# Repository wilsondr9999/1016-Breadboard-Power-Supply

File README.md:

# BreadBrick
#### The breadboard power supply *with flair*

## Why Another Breadboard Power Supply?

There's a million of these things out there, and they all work pretty much the same.  They plug in on one end of the breadboard and supply power to the voltage rails.  Many do 5V only, some have switchable 5V / 3.3V using jumpers.  Many use linear power regulators which are not terribly efficient.  Many have substantial voltage droop.  Many can't supply very much current.

I wanted something with a bit more, ummm, pizazz.  I wanted a case, not a bare PCB.  I wanted the ability to set the voltage independently for each rail, indicator lights for what voltages are set, up to 2A / 10W on each rail, and protection circuitry for those times when you plug something into the breadboard backwards.  And some efficiency so the thing doesn't get hot.

It took me a while, but I did it.

## Design

The design of the unit is actually not too complicated, there is an input section for protection and filtering, three [Texas Instruments TPS62130A](https://www.ti.com/product/TPS62130A) switching buck regulator circuits, two for the two power rails, and a 3rd that generates a dedicated 3.3V for the MCU, and an MCU section that uses the [STM32C011F4](https://www.st.com/en/microcontrollers-microprocessors/stm32c011f4.html).  The MCU is used to get user input from the buttons, drive the indicator LEDs, and control and monitor the rail regulators.

All components were selected for reasonable cost and wide availability.  However, the design is at the limit of what a hobbyist can successfully assemble.  While no parts smaller than 0603 are used, some ICs are QFN, and hand soldering these parts can be difficult for the hobbyists.  This board can be assembled by board assembly services at a reasonable cost.

## Tools and Software

Circuit design, schematics, and PCB layout were all done with [KiCad](https://www.kicad.org/).  Design of the case was done in [FreeCAD](https://www.freecad.org/).  Software code for the STM32C0 was written, compiled, and debugged using the [STM32CubeIDE](https://www.st.com/en/development-tools/stm32cubeide.html) development environment.

## Licensing

Several different licenses apply to this repository and the files within.

All schematics and circuit board designs in the project (all KiCad files), as well as all case designs (all FreeCAD files) are licensed under the [CERN Open Hardware License Version 2 - Strongly Reciprocal (CERN-OHL-S)](LICENSE-CERN-OHL-S).

All software and firmware code in the project (all ) are licensed under the [GNU Affero General Public License v3.0 (AGPL 3.0)](LICENSE-AGPL).

Documentation, Bill of Materials, pictures, and documentation (i.e. all other files not covered by the other two licenses above) are licensed under the [Creative Commons Attribution Share Alike 4.0 International License (CC-BY-SA-4.0)](LICENSE-CC-BY-SA-4.0).

These licenses form a very restrictive license for this design and this project.  This is done specifically for a reason.  That reason is that this project is for the hobbyist, and the hobbyist only.  It is for those people who want to have one of these units to be able to make one for themselves.  What it is not for is for some no-name company to produce thousands of them and make money when they had nothing to do with the design and the hard work.  These licenses force anyone who wants to do that to share anything and everything that they derive from this work so that the community and the hobbyists have it also.

## Specifications
- Input Voltage: 7V - 17V
- DC Barrel Jack: 2.5mm ID x 5.5mm OD, Center pin is positive (+)
- Max Input Current: 2A
- Output Voltage: 5V +/- 0.05V, 3.3V +/- 0.05V, switchable per rail
- Output Voltage Ripple: 25 mV at 2A load
- Max Output Current: 2A per rail
- Typical Efficiency: 88.0% at 12V input and 5V / 1A output
- Worst-Case Efficiency: 84.0% at 17V input and 3.3V / 2A output
- Worst-Case heat sink temperature: 51.1 C at full 2A load

## How To Build
#### Ordering the PCB
To order this PCB, you can submit the [Fabrication Exports.zip](KiCAD%20Project/Fabrication%20Exports/Fabrication%20Exports.zip) file (located in [KiCAD Project/Fabrication Exports/](KiCAD%20Project/Fabrication%20Exports/)) to your favorite PCB manufacturing company.  This is a 2 layer board so costs should be low.
#### Ordering the Stencil
If you want to assemble the board yourself, especially if you want to use a reflow oven, you can order a stencil using the [1016 Breadboard Power Supply-F_Paste.gbr](KiCAD%20Project/Fabrication%20Exports/1016%20Breadboard%20Power%20Supply-F_Paste.gbr) gerber layer.  This layer includes 2.5mm alignment pins on two corners, these are sized and located to fit on the [solder stencil jig](FreeCAD%20Project/Parametric%20Solder%20Stencil%20Jig/1016%20v2%20Parametric%20Solder%20Stencil%20Jig.3mf) that can be 3D-printed.  If instead you are having a PCB manufacturer assemble the SMD components for you, you do not need the solder stencil.
#### Ordering Parts
If you're assembling yourself, you'll need to order parts.  The [1016 Breadboard Power Supply.csv](KiCAD%20Project/BOM/1016%20Breadboard%20Power%20Supply.csv) file located in the [KiCAD Project/BOM/](KiCAD%20Project/BOM/) folder contains all parts and manufacturer part numbers.
#### Assembling the PCB
The [ibom.html](KiCAD%20Project/BOM/ibom.html) file located in the [KiCAD Project/BOM/](KiCAD%20Project/BOM/) folder is generated from the [KiCad Interactive BOM plug-in](https://github.com/openscopeproject/InteractiveHtmlBom), and can help you mark which parts have been placed on the board prior to reflow.

Be very careful placing the LEDs.  The silkscreen marks pin 1 of the LED, but in accordance with the [datasheets](Datasheets/[DS-006]%20Wurth%20Elektronik%20150060VS75003.pdf) for the Wurth Elektronik LEDs, the pin 1 marking is NOT the cathode as would normally be expected.

After placing components, reflow the board in a reflow oven, hot plate, or use a hot air station.
#### Through-Hole Components
You will need to solder three through-hole components -- the DC power jack (PJ-102B), and the 2x2 pin headers (J3/J4).
#### Heat Sinks
The two heat sinks are glued onto the back side of the board using thermal adhesive.  Note that this is thermal adhesive (glue), not just an ordinary thermal compound or thermal paste.  The adhesive is required, there is no other mechanical support for the heat sinks.  I successfully used the [Gennel G109 Thermal Conductive Glue](https://www.amazon.com/dp/B072MSXHJD?psc=1&ref=ppx_yo2ov_dt_b_product_details).
#### 3D Printing the Case
The case can be 3D printed using the [Case Top-Bottom.3mf](FreeCAD%20Project/Case/STL/Case%20Top-Bottom.3mf), [Button.3mf](FreeCAD%20Project/Case/STL/Button.3mf), and [LED Lens.3mf](FreeCAD%20Project/Case/STL/LED%20Lens.3mf) files and [PrusaSlicer](https://www.prusa3d.com/page/prusaslicer_424/), or if you want to slice the .stl files yourself, the .stl files are also included in the [FreeCAD Project/Case/STL](FreeCAD%20Project/Case/STL/) folder.  Printing settings are as follows:
- 0.12mm Layer Height
- 0.4mm Nozzle
- PETG material, do not use PLA.  The snap-together design needs a flexible plastic, PLA is too brittle and will likely break when trying to snap together the case.  Also, PLA is not as temperature-resistant as PETG, and the heat sinks could cause problems with PLA.
- For the LED lenses, you will need a clear PETG filament.  I have had good results with [PolyMaker PolyLite Clear PETG](https://us.polymaker.com/products/polylite-petg?variant=41266031099961).
- Supports are not required, but both case halves should be printed with their flat surface on the print bed.  You may need to turn the upper case half so that the flat top is on the print bed.  The LED lenses need to be turned so that the larger side is down on the print bed.
- The upper case half prints with a thin bridge covering the LED lens holes, you will need to clean out the bridges with a hobbyist knife prior to inserting the LED lenses.
- It is critical that the buttons are printed to accurate dimensions as the clearances and travel are very small.  Print the buttons at a very slow speed with adequate time for each layer to cool to prevent any warping or distortion.  The .3mf file already has these settings pre-set.
#### Programming Firmware to the STM32
The STM32C011F4 firmware is the [1016 Breadboard Power Supply.elf](STM32%20Project/Debug/1016%20Breaadboard%20Power%20Supply.elf) file located in the [(STM32 Project/Debug/]((STM32%20Project/Debug/) folder.  This can be programmed to the STM32C011F4 using the [ST-Link/V2](https://www.st.com/en/development-tools/st-link-v2.html) debugger and the [Tag-Connect ARM20-CTX SWD Solution](https://www.tag-connect.com/debugger-cable-selection-installation-instructions/st-link-v2#49_126_145).  The 6-pin Tag-Connect connector connects with the J2 connector on the PCB, and the [STM32CubeProgrammer](https://www.st.com/en/development-tools/stm32cubeprog.html) software can write the firmware to the MCU.

Note that if you order the Tag-Connect SWD solution, you need the "No-Legs" version of the package that includes the TC-2030-IDC-NL cable.  The version of the cable with legs (TC-2030-IDC) will not properly fit this PCB.
#### Assembling the Unit
Once the PCB has been populated and soldered with the SMD and THT components, the heat sinks are attached with the thermal adhesive, and the case parts have been printed you can assemble the entire unit.
- Turn the upper half of the case upside down, and insert the two buttons, aligning the base of the buttons so that they will fit over the SMD switches on the PCB.
- Place the PCB into the top side of the case with the components towards the buttons and the heat sinks protruding.  Ensure the base of the buttons goes over the SMD switches on the PCB.  Hold the PCB against the support columns with your fingers.
- Test the buttons on the other side of the case and ensure you can feel them actuate the switches and that the switches are NOT pressed when the PCB is seated against the support columns.
- If the switches are not getting pressed when you press the button, the buttons dimensions are too small.  Re-check your print settings.
- If the switches are getting pressed before the PCB is seated against the support columns, the buttons dimensions are too large.  Re-check your print settings.
- Once you are confident that the buttons are the correct size and will work, remove the PCB from the top case half.
- Tape the buttons in place on the top side.  Fold the tape around the protruding button so that the button is at the top of it's travel (most protrusion).
- Insert the PCB into the case bottom with the components up and the heat sinks down.  The heat sinks will fit inside the cooling passages, and the holes in the PCB will fit on the support pins.
- Carefully fit the top half with the taped buttons onto the bottom half, and carefully get the two halves to mate and snap together.
- Remove the tape from the buttons and re-check that the buttons are working properly.  If you need to get the case apart again, you will need to use a [spudger](https://www.amazon.com/MMOBIEL-Pieces-Professional-Spudger-Toolkit/dp/B00UNBTM5U/ref=sr_1_4?keywords=spudger&sr=8-4) to pry the case apart.

## Using the Breadboard Power Supply
Plug the unit into your breadboard into the power rails.  As you're looking at the unit, the power arms/leads should point towards your right.  In this position, the TOP pins of each rail (furthest away from you) are the positive voltage, the BOTTOM pins of each rail (closest to you) are the reference voltage (ground).  Orient your breadboard so that the red/positive row of pins aligns with the positive pin of the unit (away from you).  If your breadboard is turned 180 degrees, the colors of the power rails will be opposite, and will cause confusion.

Power the unit using a DC barrel jack and power supply.  The jack is a standard 2.5mm x 5.5mm DC barrel jack, the center pin is the positive lead.  The unit has reverse power protection, so if your power supply uses ground for the center pin, you will not damage the unit, but it will not power on.  Your power supply should be between 7V and 17V output, and should provide at least 24W of power.  The standard supply that the unit was designed for is a [12V, 2A supply](https://www.amazon.com/Chanzon-Switching-Adapter-100-240V-Transformer/dp/B07HNL5D56/ref=sr_1_19?keywords=12v+2a+power+supply&sr=8-19).  

Once the unit is powered on, it will self-test all LEDs.  You should see them sequentially light.

The left-most LED is the power-on LED, and indicates that input power is being received and is the correct voltage and polarity.  The LED remains green at all times when input power is supplied.

The top and bottom right-most LEDs indicate what voltage has been selected for the top rail and the bottom rail, respectively.  The LED is green when the rail has been selected for 5V output.  The LED is yellow when the rail has been selected for 3.3V output.

To configure the voltage setting, use the top-most button (colored green in the FreeCAD drawings).  Each press of the button cycles between the 4 combinations of rail voltages as follows:
1. Both rails 5V (LEDs green/green).
2. Top rail 3.3V / bottom rail 5V (LEDs yellow/green).
3. Top rail 5V / bottom rail 3.3V (LEDs green/yellow).
4. Both rails 3.3V (LEDs yellow/yellow).

Once you have selected the required voltage for your breadboard, turn the output on by pressing the bottom-most button (colored orange in the FreeCAD drawings).  The middle LED on the right will light orange to indicate that the output is on.  The unit begins monitoring the output power 50 msec after the output is turned on, and monitors the "Power Good" signal from both rail regulators.  If the output is subjected to a short circuit, an overcurrent condition, or the regulator temperatures get too high, the "power no good" signal from the regulators will be sensed and the MCU will turn off the output power, turn off all LEDs, and blink the middle LED red for 5 seconds.  The unit will then reset with the output power off.  This error condition can also occur if the input power source has problems, including undervoltage.  If this occurs, check the ratings on your input power source.

Press the bottom-most button again to turn the output power off on both rails.

The voltage configuration for the rails cannot be changed when the output is on.  When the output is on, pressing the top-most button will have no effect.  You must turn the output off using the bottom-most button before the voltage configuration can be changed.

## Caveats
The unit does **NOT** remember your voltage configuration setting between power cycles.  When input power is cycled, the unit will start up in a 5V/5V configuration.  If your breadboard needs 3.3V power on one or both of the rails, you will need to double-check and change the voltage configuration on each power-up before you turn the output power on.

Enjoy the unit, and happy breadboarding!

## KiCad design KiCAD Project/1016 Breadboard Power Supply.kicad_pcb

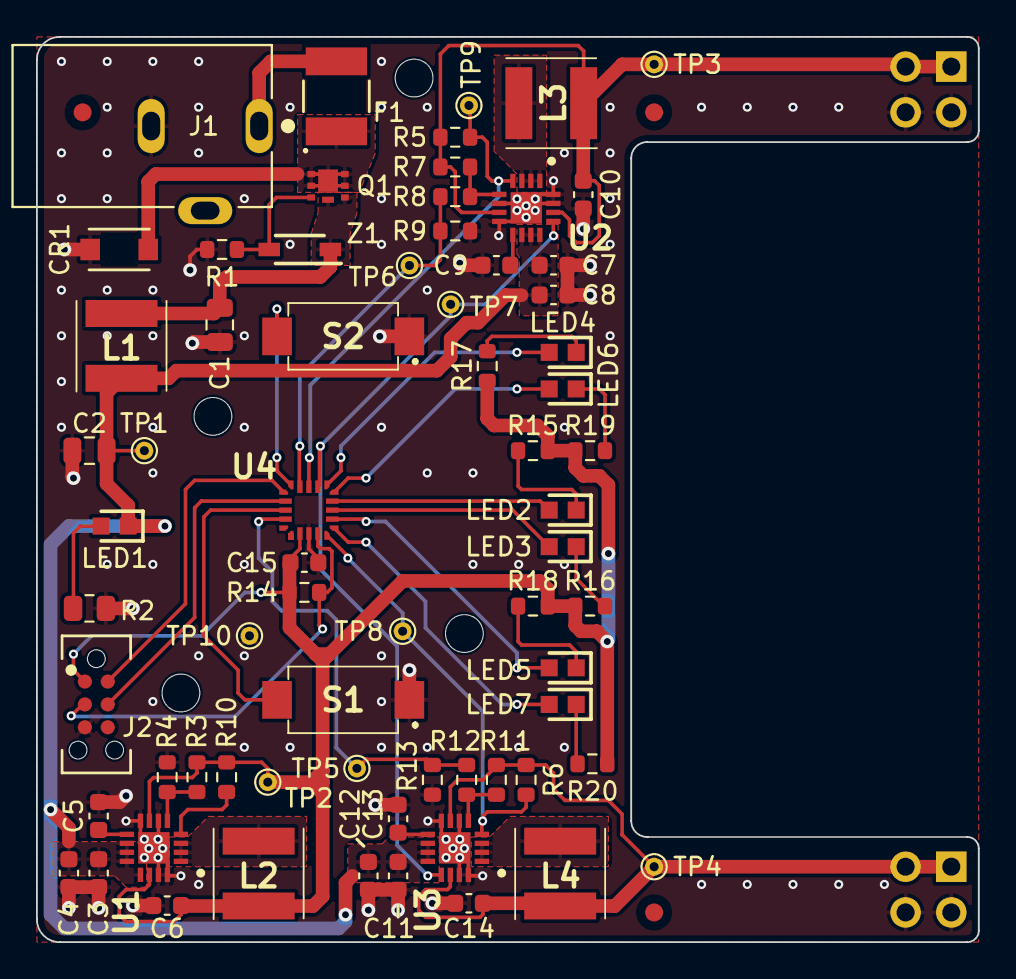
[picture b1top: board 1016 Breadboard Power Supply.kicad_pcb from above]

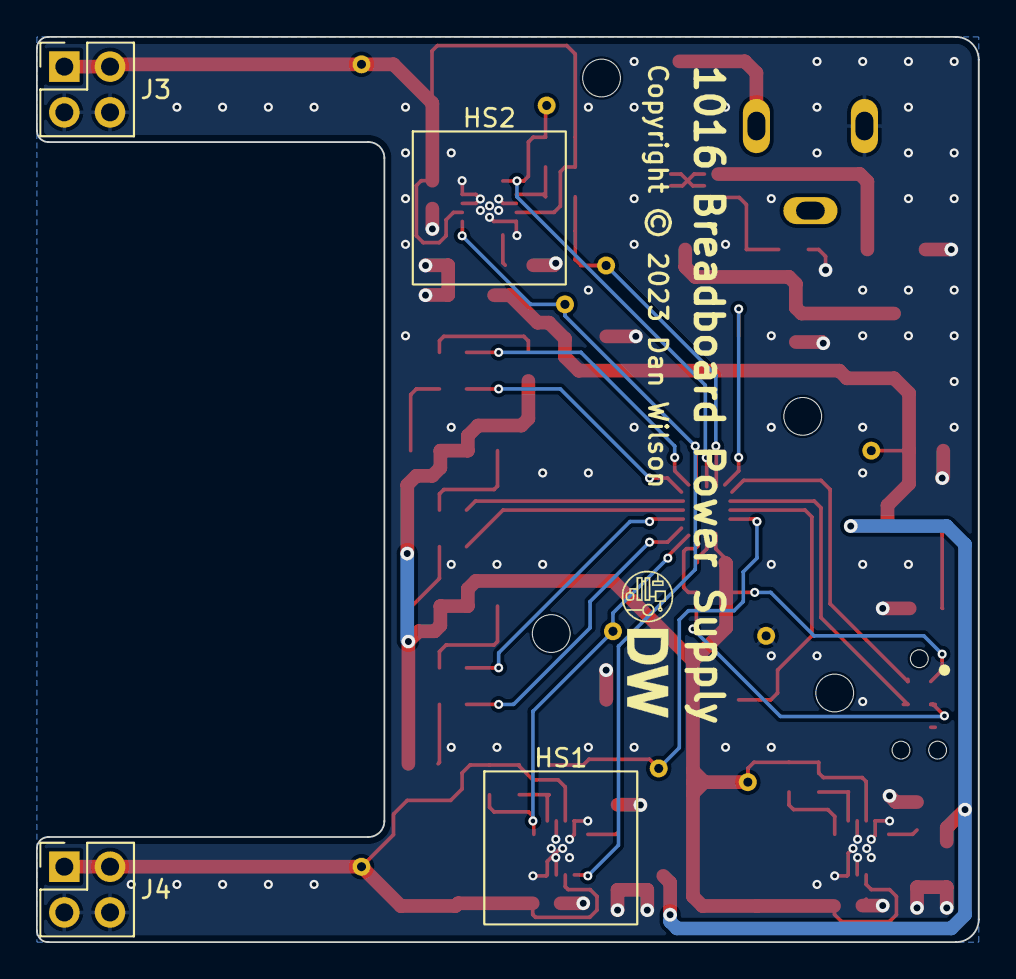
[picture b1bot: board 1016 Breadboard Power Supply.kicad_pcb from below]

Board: 2 copper layers, 52.3 x 50.3 mm, 82 parts (5 on the bottom side), 42 nets.

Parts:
C1, C2: 22µ; C_0805_2012Metric
C3, C7, C11: 10µF; C_0603_1608Metric
C4, C8, C12, C15: 100n; C_0603_1608Metric
C5, C9, C13: 3n3; C_0603_1608Metric
C6, C10, C14: 22µ; C_0603_1608Metric
CR1: SMF17CA; SOD-123F_LTF
F1: SMD1812B110TF; FUSE_SMD1812B110TF_YAG
FID1, FID2, FID3: Fiducial; Fiducial_1mm_Mask2mm
H1, H2, H3, H4: MountingHole; MountingHole_2.1mm
HS1, HS2: Heat Sink; HSB01-080808
J1: PJ-102B; CUI_PJ-102B
J2: TC2030-IDC-NL; CONN_TC2030-IDC-NL_TGC
J3, J4: Pin Hdr 2x2; PinHeader_2x02_P2.54mm_Vertical
L1, L2, L3, L4: VLS5045EX-2R2N; VLS5045EX330M
LED1, LED4, LED5: 150060VS75003; LEDC1608X80N
LED2: 150060RS75003; LEDC1608X80N
LED3: 150060AS75003; LEDC1608X80N
LED6, LED7: 150060YS75003; LEDC1608X80N
P1: DW_PCB_Logo
P2, P3: Solder_Stencil_Alignment_Pin
Q1: BUK6D120-60PX; BUK6D12060PX
R1: 1K91; R_0603_1608Metric
R2: 2K; R_0805_2012Metric
R3: 100K; R_0603_1608Metric
R4: 31K6; R_0603_1608Metric
R5, R6, R10, R14: 10K; R_0603_1608Metric
R7, R11: 220K; R_0603_1608Metric
R8, R12: 42K2; R_0603_1608Metric
R9, R13: 28K; R_0603_1608Metric
R15: 365; R_0603_1608Metric
R16: 402; R_0603_1608Metric
R17, R18: 210; R_0603_1608Metric
R19, R20: 887; R_0603_1608Metric
S1, S2: Tactile Switch 6mm; PTS636SK25JSMTRLFS
TP1, TP2, TP3, TP4, TP5, TP6, TP7, TP8, TP9, TP10: TestPoint; TestPoint_THTPad_D1.0mm_Drill0.5mm
U1, U2, U3: TPS62130ARGTR; QFN50P300X300X100-17N-D
U4: STM32C011F4U6TR; UFQFPN20_3X3_STM
Z1: MMSZ5231B-7-F; SOD3716X145N

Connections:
/Input Power/GND: C1.2, C2.2, C3.2, C4.2, C5.1, C6.2, C7.2, C8.2, C9.1, C10.2, C11.2, C12.2, C13.1, C14.2, C15.2, CR1.2, J1.2, J2.5, J3.3, J3.4, J4.3, J4.4, R1.2, R2.2, R4.2, R9.2, R13.2, S1.1 (COM), S2.1 (COM), TP10.1, U1.6 (AGND), U1.8 (DEF), U1.15 (PGND_1), U1.16 (PGND_2), U1.17 (EP), U2.6 (AGND), U2.8 (DEF), U2.15 (PGND_1), U2.16 (PGND_2), U2.17 (EP), U3.6 (AGND), U3.8 (DEF), U3.15 (PGND_1), U3.16 (PGND_2), U3.17 (EP), U4.3 (VSS/VSSA)
/Input Power/RPPgate: Q1.3 (G), R1.1, Z1.2 (A)
/Input Power/VCC: C2.1, C3.1, C4.1, C7.1, C8.1, C11.1, C12.1, L1.2, LED1.1 (A), TP1.1, U1.10 (AVIN), U1.11 (PVIN_1), U1.12 (PVIN_2), U1.13 (EN), U2.10 (AVIN), U2.11 (PVIN_1), U2.12 (PVIN_2), U3.10 (AVIN), U3.11 (PVIN_1), U3.12 (PVIN_2)
/Input Power/Vfused: CR1.1, F1.2, Q1.1 (D_1), Q1.2 (D_2), Q1.5 (D_3), Q1.6 (D_4), Q1.7 (D_5)
/Input Power/Vin: F1.1, J1.1
/Input Power/Vprot: C1.1, L1.1, Q1.4 (S_1), Q1.8 (S_2), Z1.1 (K)
/MCU Control/3V3BLED_A: LED7.1 (A), R20.1
/MCU Control/3V3BLED_Sig: LED7.2 (K), U4.6 (PA1)
/MCU Control/3V3TLED_A: LED6.1 (A), R19.1
/MCU Control/3V3TLED_Sig: LED6.2 (K), U4.10 (PA5)
/MCU Control/5VBLED_A: LED5.1 (A), R18.1
/MCU Control/5VBLED_Sig: LED5.2 (K), U4.7 (PA2)
/MCU Control/5VTLED_A: LED4.1 (A), R17.1
/MCU Control/5VTLED_Sig: LED4.2 (K), U4.11 (PA6)
/MCU Control/Btn_Config: S2.2 (NO), U4.15 (PA12[PA10])
/MCU Control/Btn_OutputEn: S1.2 (NO), U4.18 (PB6)
/MCU Control/Enable_Output: TP7.1, U2.13 (EN), U3.13 (EN), U4.12 (PA7)
/MCU Control/ErrorLED_A: LED2.1 (A), R15.1
/MCU Control/ErrorLED_Sig: LED2.2 (K), U4.9 (PA4)
/MCU Control/NRST: J2.3, R14.2, U4.4 (PF2-NRST)
/MCU Control/OutputLED_A: LED3.1 (A), R16.1
/MCU Control/OutputLED_Sig: LED3.2 (K), U4.8 (PA3)
/MCU Control/PGood_RailB: R6.2, TP8.1, U3.4 (PG), U4.5 (PA0)
/MCU Control/PGood_RailT: R5.2, TP9.1, U2.4 (PG), U4.13 (PA8)
/MCU Control/SWDCLK: J2.4, U4.17 (PA14-BOOT0)
/MCU Control/SWDIO: J2.2, U4.16 (PA13)
/MCU Control/SelectVrailB: R12.2, R13.1, TP5.1, U4.19 (PB7)
/MCU Control/SelectVrailT: R8.2, R9.1, TP6.1, U4.14 (PA11[PA9])
/MCU Control/Vmcu: C6.1, C15.1, J2.1, L2.2, R3.1, R10.2, R14.1, R15.2, R16.2, R17.2, R18.2, R19.2, R20.2, TP2.1, U1.7 (FSW), U1.14 (VOS), U4.2 (VDD/VDDA)
/MCU Power Regulator/MCUReg_FB: R3.2, R4.1, U1.5 (FB)
/MCU Power Regulator/MCUReg_SS: C5.2, U1.9 (SS/TR)
/MCU Power Regulator/MCUReg_Sw_Out: L2.1, U1.1 (SW_1), U1.2 (SW_2), U1.3 (SW_3)
/MCU Power Regulator/PGood_MCU: R10.1, U1.4 (PG)
/Rail B Power Regulator/RailBReg_FB: R11.2, R12.1, U3.5 (FB)
/Rail B Power Regulator/RailBReg_SS: C13.2, U3.9 (SS/TR)
/Rail B Power Regulator/RailBReg_Sw_Out: L4.1, U3.1 (SW_1), U3.2 (SW_2), U3.3 (SW_3)
/Rail B Power Regulator/VrailB: C14.1, J4.1, J4.2, L4.2, R6.1, R11.1, TP4.1, U3.7 (FSW), U3.14 (VOS)
/Rail Output/VrailT: C10.1, J3.1, J3.2, L3.2, R5.1, R7.1, TP3.1, U2.7 (FSW), U2.14 (VOS)
/Rail T Power Regulator/RailTReg_FB: R7.2, R8.1, U2.5 (FB)
/Rail T Power Regulator/RailTReg_SS: C9.2, U2.9 (SS/TR)
/Rail T Power Regulator/RailTReg_Sw_Out: L3.1, U2.1 (SW_1), U2.2 (SW_2), U2.3 (SW_3)
unnamed: LED1.2 (K), R2.1

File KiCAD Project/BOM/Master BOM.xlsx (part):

1016 Breadboard Power Supply Master BOM
Item ID | Sheet | Description | Spec | Sch Ref | Qty | Value | DNP | Height | Manufacturer | Mfr Part Num | Mouser Part Num | LCSC Part Num |  | [4] DL SF3 | [5] Import | [6] Place | [7] Update
1 | Input Power | Input Power Jack | 2.5mm, 2.5A, 24V | J1 | 1 | PJ-102B | 0 | 11 | CUI Devices | PJ-102B | 490-PJ-102B |  |  | X | X | X | X
2 | Input Power | PTC Resettable Fuse | Ihold 3A, Itrip 6A | F1 | 1 | PTC 3A | 0 | 1.6 | Yageo-Brightking | SMD1812B300TFT | 603-SMD1812B300TFT | C269149 |  | X | X | X | X
3 | Input Power | TVS Suppression Diode | Vrw 17V, Vcl 27V | CR1 | 1 | SMF17CA | 0 | 1 | Littlefuse | SMF17CA | 576-SMF17CA | C3719828 |  | X | X | X | X
4 | Input Power | RPP MOSFET | P-Ch 60V 8A | Q1 | 1 | BUK6D120-60PX | 0 | 0.65 | Nexperia | BUK6D120-60PX | 771-BUK6D120-60PX | C503628 |  | X | X | X | X
5 | Input Power | RPP Zener Diode | 5.1V 5% 500mW | Z1 | 1 | MMSZ5231B-7-F | 0 | 1.05 | Diodes Inc | MMSZ5231B-7-F | 621-MMSZ5231B-7-F | C85181 |  | X | X | X | X
6 | Input Power | Power On LED | Grn 570nm | LED1 | 1 | 150060VS75003 | 0 | 0.7 | Wurth Elektronik | 150060VS75003 | 710-150060VS75003 | C965852 |  | X | X | X | X
7 | Input Power | RPP Zener Resistor | 1K91 100mW | R1 | 1 | 1K91 | 0 | 0.45 | Yageo | RC0603FR-071K91L | 603-RC0603FR-071K91L | C185353 |  | - | - | X | X
8 | Input Power | Power On LED Resistor | 2K 125mW | R2 | 1 | 2K | 0 | 0.5 | Yageo | RC0805FR-072KL | 603-RC0805FR-072KL | C114572 |  | - | - | X | X
9 | Input Power | Pi Filter Capacitor | 22µ 25V | C1, C2 | 2 | 22µ | 0 | 1.25 | Samsung | CL21A226MAYNNNE | 187-CL21A226MAYNNNE | C602037 |  | - | - | X | X
10 | Input Power | Pi Filter Inductor | 2.2µ 4.7A 22mΩ | L1 | 1 | 2.2µ | 0 | 4.5 | TDK | VLS5045EX-2R2N | 810-VLS5045EX-2R2N | C434831 |  | X | X | X | X
11 | MCU Power Regulator | Regulator for MCU 3V3 | 2.5MHz Buck Reg | U1 | 1 | TPS62130A | 0 | 1 | Texas Instruments | TPS62130ARGTR | 595-TPS62130ARGTR | C337502 |  | X | X | X | X
12 | MCU Power Regulator | Feedback Rtop | 100K 100mW | R3 | 1 | 100K | 0 | 0.45 | Yageo | RC0603FR-07100KL | 603-RC0603FR-07100KL | C14675 |  | - | - | X | X
13 | MCU Power Regulator | Feedback Rbot | 31K6 100mW | R4 | 1 | 31K6 | 0 | 0.45 | Yageo | RC0603FR-0731K6L | 603-RC0603FR-0731K6L | C185339 |  | - | - | X | X
14 | MCU Power Regulator | Input Capacitor | 10µ 25V | C3 | 1 | 10µ | 0 | 0.8 | Samsung | CL10A106MA8NRNC | 187-CL10A106MA8NRNC | C96446 |  | - | - | X | X
15 | MCU Power Regulator | Bypass Capacitor | 100n 25V | C4 | 1 | 100n | 0 | 0.8 | Samsung | CL10B104KA8NNNC | 187-CL10B104KA8NNNC | C1590 |  | - | - | X | X
16 | MCU Power Regulator | Startup Capacitor | 3n3 25V | C5 | 1 | 3n3 | 0 | 0.8 | Yageo | CC0603KRX7R8BB332 | 603-CC603KRX7R8BB332 | C519423 |  | - | - | X | X
17 | MCU Power Regulator | Output Capacitor | 22µ 6V3 | C6 | 1 | 22µ | 0 | 0.8 | Samsung | CL10A226MQ8NRNE | 187-CL10A226MQ8NRNE | C159801 |  | - | - | X | X
18 | MCU Power Regulator | Output Discharge Resistor | 10K 100mW | R10 | 1 | 10K | 0 | 0.45 | Yageo | RC0603FR-0710KL | 603-RC0603FR-0710KL | C98220 |  | - | - | X | X
19 | Rail T Power Regulator | Regulator for Top Rail | 2.5MHz Buck Reg | U2 | 1 | TPS62130 | 0 | 1 | Texas Instruments | TPS62130RGTR | 595-TPS62130RGTR | C43590 |  | X | X | X | X
20 | Rail T Power Regulator | Feedback Rtop | 220K 100mW | R7 | 1 | 220K | 0 | 0.45 | Yageo | RC0603FR-07220KL | 603-RC0603FR-07220KL | C123420 |  | - | - | X | X
21 | Rail T Power Regulator | Feedback Rbot1 | 42K2 100mW | R8 | 1 | 42K2 | 0 | 0.45 | Yageo | RC0603FR-0742K2L | 603-RC0603FR-0742K2L | C273741 |  | - | - | X | X
22 | Rail T Power Regulator | Feedback Rbot2 | 28K 100mW | R9 | 1 | 28K | 0 | 0.45 | Yageo | RC0603FR-0728KL | 603-RC0603FR-0728KL | C273777 |  | - | - | X | X
23 | Rail T Power Regulator | Input Capacitor | 10µ 25V | C7 | 1 | 10µ | 0 | 0.8 | Samsung | CL10A106MA8NRNC | 187-CL10A106MA8NRNC | C96446 |  | - | - | X | X
24 | Rail T Power Regulator | Bypass Capacitor | 100n 25V | C8 | 1 | 100n | 0 | 0.8 | Samsung | CL10B104KA8NNNC | 187-CL10B104KA8NNNC | C1590 |  | - | - | X | X
25 | Rail T Power Regulator | Startup Capacitor | 3n3 25V | C9 | 1 | 3n3 | 0 | 0.8 | Yageo | CC0603KRX7R8BB332 | 603-CC603KRX7R8BB332 | C519423 |  | - | - | X | X
26 | Rail T Power Regulator | Output Capacitor | 22µ 6V3 | C10 | 1 | 22µ | 0 | 0.8 | Samsung | CL10A226MQ8NRNE | 187-CL10A226MQ8NRNE | C159801 |  | - | - | X | X
27 | Rail T Power Regulator | Output Discharge Resistor | 10K 100mW | R5 | 1 | 10K | 0 | 0.45 | Yageo | RC0603FR-0710KL | 603-RC0603FR-0710KL | C98220 |  | - | - | X | X
28 | Rail B Power Regulator | Regulator for Bottom Rail | 2.5MHz Buck Reg | U3 | 1 | TPS62130 | 0 | 1 | Texas Instruments | TPS62130RGTR | 595-TPS62130RGTR | C43590 |  | X | X | X | X
29 | Rail B Power Regulator | Feedback Rtop | 220K 100mW | R11 | 1 | 220K | 0 | 0.45 | Yageo | RC0603FR-07220KL | 603-RC0603FR-07220KL | C123420 |  | - | - | X | X
30 | Rail B Power Regulator | Feedback Rbot1 | 42K2 100mW | R12 | 1 | 42K2 | 0 | 0.45 | Yageo | RC0603FR-0742K2L | 603-RC0603FR-0742K2L | C273741 |  | - | - | X | X
31 | Rail B Power Regulator | Feedback Rbot2 | 28K 100mW | R13 | 1 | 28K | 0 | 0.45 | Yageo | RC0603FR-0728KL | 603-RC0603FR-0728KL | C273777 |  | - | - | X | X
32 | Rail B Power Regulator | Input Capacitor | 10µ 25V | C11 | 1 | 10µ | 0 | 0.8 | Samsung | CL10A106MA8NRNC | 187-CL10A106MA8NRNC | C96446 |  | - | - | X | X
33 | Rail B Power Regulator | Bypass Capacitor | 100n 25V | C12 | 1 | 100n | 0 | 0.8 | Samsung | CL10B104KA8NNNC | 187-CL10B104KA8NNNC | C1590 |  | - | - | X | X
34 | Rail B Power Regulator | Startup Capacitor | 3n3 25V | C13 | 1 | 3n3 | 0 | 0.8 | Yageo | CC0603KRX7R8BB332 | 603-CC603KRX7R8BB332 | C519423 |  | - | - | X | X
35 | Rail B Power Regulator | Output Capacitor | 22µ 6V3 | C14 | 1 | 22µ | 0 | 0.8 | Samsung | CL10A226MQ8NRNE | 187-CL10A226MQ8NRNE | C159801 |  | - | - | X | X
36 | Rail B Power Regulator | Output Discharge Resistor | 10K 100mW | R6 | 1 | 10K | 0 | 0.45 | Yageo | RC0603FR-0710KL | 603-RC0603FR-0710KL | C98220 |  | - | - | X | X
37 | MCU Control | Microcontroller | 48MHz ARM M0 | U4 | 1 | STM32C011F4U6TR | 0 | 0.55000000000000004 | ST Micro | STM32C011F4U6TR | 511-STM32C011F4U6TR | C5456188 |  | X | X | X | X
38 | MCU Control | SWD Pogo Connector | 6-Pin SWD | J2 | 1 | TC2030-IDC | 0 | 0 | Tag-Connect | TC2030-IDC |  |  |  | X | X | X | X
39 | MCU Control | Output Enable | 50mA 12Vdc 250gf | S1 | 1 | Tactile Switch 6mm | 0 | 2.7 | C & K COMPONENTS | PTS636 SK25J SMTR LFS | 611-PTS636SK25JSMTRL | C2800965 |  | X | X | X | X
40 | MCU Control | Config Btn | 50mA 12Vdc 250gf | S2 | 1 | Tactile Switch 6mm | 0 | 2.7 | C & K COMPONENTS | PTS636 SK25J SMTR LFS | 611-PTS636SK25JSMTRL | C2800965 |  | X | X | X | X
41 | MCU Control | Error LED | Red 625nm | LED2 | 1 | 150060RS75003 | 0 | 0.7 | Wurth Elektronik | 150060RS75003 | 710-150060RS75003 | C965799 |  | X | X | X | X
42 | MCU Control | Output LED | Amber 605nm | LED3 | 1 | 150060AS75003 | 0 | 0.7 | Wurth Elektronik | 150060AS75003 | 710-150060AS75003 | C965801 |  | X | X | X | X
43 | MCU Control | 5V Top Rail LED | Green 570nm | LED4 | 1 | 150060VS75003 | 0 | 0.7 | Wurth Elektronik | 150060VS75003 | 710-150060VS75003 | C965852 |  | X | X | X | X
44 | MCU Control | 5V Bottom Rail LED | Yellow 590nm | LED5 | 1 | 150060YS75003 | 0 | 0.7 | Wurth Elektronik | 150060YS75003 | 710-150060YS75003 | C965802 |  | X | X | X | X
45 | MCU Control | 3V3 Top Rail LED | Green 570nm | LED6 | 1 | 150060VS75003 | 0 | 0.7 | Wurth Elektronik | 150060VS75003 | 710-150060VS75003 | C965852 |  | X | X | X | X
46 | MCU Control | 3V3 Bottom Rail LED | Yellow 590nm | LED7 | 1 | 150060YS75003 | 0 | 0.7 | Wurth Elektronik | 150060YS75003 | 710-150060YS75003 | C965802 |  | X | X | X | X
47 | MCU Control | Error LED Resistor | 365 100mW | R15 | 1 | 365 | 0 | 0.45 | Yageo | AC0603FR-07365RL | 603-AC0603FR-07365RL | C227839 |  | X | X | X | X
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
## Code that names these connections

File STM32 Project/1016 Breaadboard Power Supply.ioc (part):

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Mcu.Name=STM32C011F(4-6)Ux
Mcu.Package=UFQFPN20
Mcu.UserName=STM32C011F4Ux
PA0.GPIOParameters=GPIO_Label
PA0.GPIO_Label=PGood_RailB
PA0.Signal=GPIO_Input
PA1.GPIOParameters=PinState,GPIO_PuPd,GPIO_Label,GPIO_ModeDefaultOutputPP
PA1.GPIO_Label=LED_3V3B
PA1.GPIO_ModeDefaultOutputPP=GPIO_MODE_OUTPUT_OD
PA1.GPIO_PuPd=GPIO_NOPULL
PA1.PinState=GPIO_PIN_SET
PA1.Signal=GPIO_Output
PA11\ [PA9].GPIOParameters=PinState,GPIO_PuPd,GPIO_Label,GPIO_ModeDefaultOutputPP
PA11\ [PA9].GPIO_Label=Select_VRailT
PA11\ [PA9].GPIO_ModeDefaultOutputPP=GPIO_MODE_OUTPUT_OD
PA11\ [PA9].GPIO_PuPd=GPIO_NOPULL
PA11\ [PA9].PinState=GPIO_PIN_SET
PA11\ [PA9].Signal=GPIO_Output
PA12\ [PA10].GPIOParameters=GPIO_PuPd,GPIO_Label
PA12\ [PA10].GPIO_Label=Btn_Config
PA12\ [PA10].GPIO_PuPd=GPIO_PULLUP
PA12\ [PA10].Signal=GPIO_Input
PA13.Mode=Serial_Wire
PA13.Signal=DEBUG_SWDIO
PA14-BOOT0.Mode=Serial_Wire
PA14-BOOT0.Signal=DEBUG_SWCLK
PA2.GPIOParameters=PinState,GPIO_PuPd,GPIO_Label,GPIO_ModeDefaultOutputPP
PA2.GPIO_Label=LED_5VB
PA2.GPIO_ModeDefaultOutputPP=GPIO_MODE_OUTPUT_OD
PA2.GPIO_PuPd=GPIO_NOPULL
PA2.PinState=GPIO_PIN_SET
PA2.Signal=GPIO_Output
PA3.GPIOParameters=PinState,GPIO_PuPd,GPIO_Label,GPIO_ModeDefaultOutputPP
PA3.GPIO_Label=LED_Output
PA3.GPIO_ModeDefaultOutputPP=GPIO_MODE_OUTPUT_OD
PA3.GPIO_PuPd=GPIO_NOPULL
PA3.PinState=GPIO_PIN_SET
PA3.Signal=GPIO_Output
PA4.GPIOParameters=PinState,GPIO_PuPd,GPIO_Label,GPIO_ModeDefaultOutputPP
PA4.GPIO_Label=LED_Error
PA4.GPIO_ModeDefaultOutputPP=GPIO_MODE_OUTPUT_OD
PA4.GPIO_PuPd=GPIO_NOPULL
PA4.PinState=GPIO_PIN_SET
PA4.Signal=GPIO_Output
PA5.GPIOParameters=PinState,GPIO_PuPd,GPIO_Label,GPIO_ModeDefaultOutputPP
PA5.GPIO_Label=LED_3V3T
PA5.GPIO_ModeDefaultOutputPP=GPIO_MODE_OUTPUT_OD
PA5.GPIO_PuPd=GPIO_NOPULL
PA5.PinState=GPIO_PIN_SET
PA5.Signal=GPIO_Output
PA6.GPIOParameters=PinState,GPIO_PuPd,GPIO_Label,GPIO_ModeDefaultOutputPP
PA6.GPIO_Label=LED_5VT
PA6.GPIO_ModeDefaultOutputPP=GPIO_MODE_OUTPUT_OD
PA6.GPIO_PuPd=GPIO_NOPULL
PA6.PinState=GPIO_PIN_SET
PA6.Signal=GPIO_Output
PA7.GPIOParameters=GPIO_Label
PA7.GPIO_Label=Output_Enable
PA7.Signal=GPIO_Output
PA8.GPIOParameters=GPIO_Label
PA8.GPIO_Label=PGood_RailT
PA8.Signal=GPIO_Input
PB6.GPIOParameters=GPIO_PuPd,GPIO_Label
PB6.GPIO_Label=Btn_OutputEn
PB6.GPIO_PuPd=GPIO_PULLUP
PB6.Signal=GPIO_Input
PB7.GPIOParameters=PinState,GPIO_PuPd,GPIO_Label,GPIO_ModeDefaultOutputPP
PB7.GPIO_Label=Select_VRailB
PB7.GPIO_ModeDefaultOutputPP=GPIO_MODE_OUTPUT_OD
PB7.GPIO_PuPd=GPIO_NOPULL
PB7.PinState=GPIO_PIN_SET
PB7.Signal=GPIO_Output
RCC.HSE_VALUE=8000000
RCC.SYSCLKFreq_VALUE=12000000
board=custom

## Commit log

2023-10-08 V1.0.0.0
    Final version 1, sent for fabrication.
2023-10-23 v1.1.0.0
    Code bugs fixed and notes made for additional changes for version 2.
2023-10-23 Update LICENSE
2023-10-29 V1.1.0.1
    Created .private directory for private notes.
2023-10-30 v2.0.0.0
    1016 Breadboard Power Supply v2
    - Change FSW connection to the Vout on all regulators
    - Change regulator to TPS62130A so that PG pin goes low on thermal shutdown and UVLO
    - Change PG pullup to be a resistor at the regulator vice pullup within STM32 so that it can be actively discharged
    - Remove resistor across rail outputs for discharging to improve efficiency
    - Change board dimensions to correct span
2023-11-12 v2.0.0.1
    Version 2 Final
2023-11-21 v2.1.0.0
    Full prototype, working 3D printed case.
2023-11-26 v2.1.1.0
    Add images, update README.md, remove old / backup / v1 files.
2023-11-26 v2.1.1.1
    Add images, update README.md, clean up and remove backups / v1 files.
2023-11-26 v2.1.1.2
    Add images, update README.md, clean up and remove backups / v1 files.
2023-11-26 v2.1.1.3
    Add images, update README.md, clean up and remove backups / v1 files.
2023-11-26 V2.1.1.4
    Add images, update README.md, clean up and remove backups / v1 files.
2023-11-26 v2.1.1.5
    Add images, update README.md, clean up and remove backups / v1 files.

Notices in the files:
KiCAD Project/1016 Breadboard Power Supply.kicad_pcb:
Copyright © 2023, Dan Wilson
